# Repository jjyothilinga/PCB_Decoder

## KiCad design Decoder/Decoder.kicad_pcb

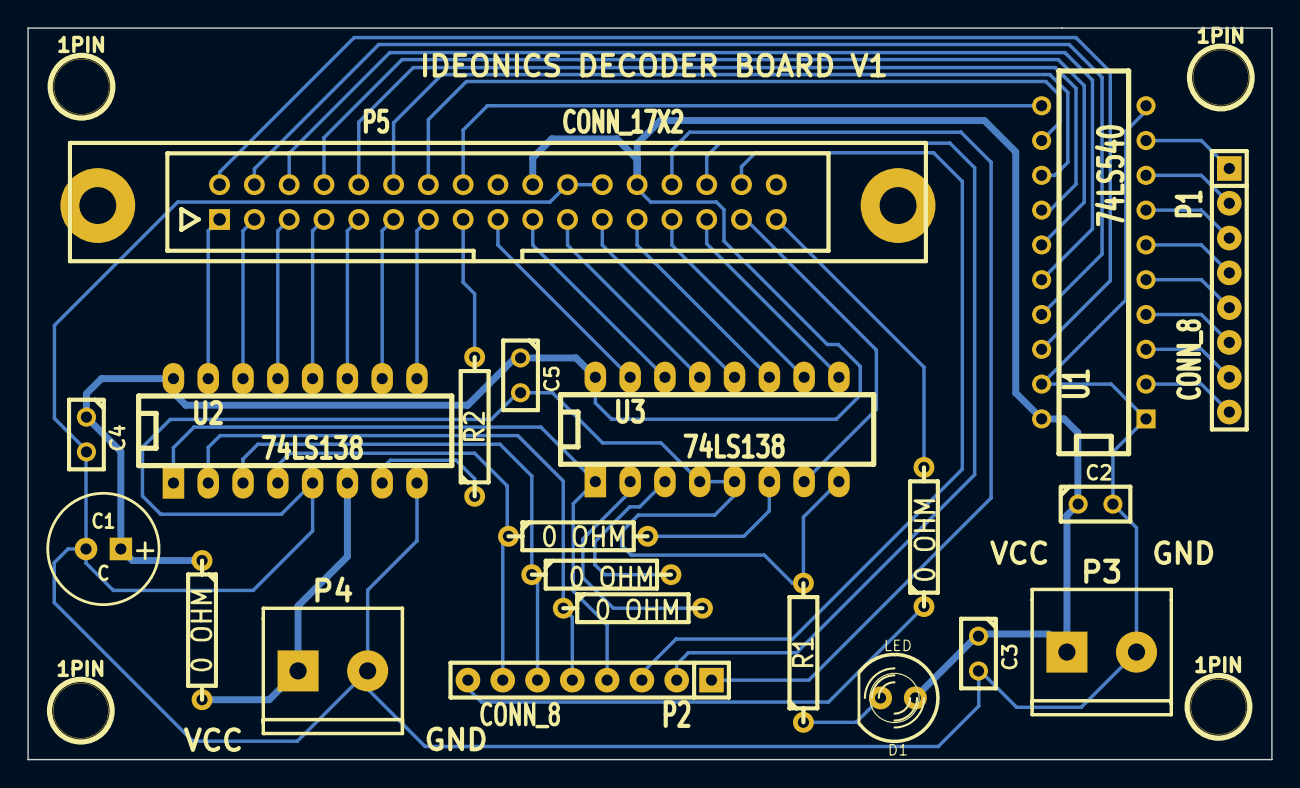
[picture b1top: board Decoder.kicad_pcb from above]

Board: 2 copper layers, 90.8 x 53.4 mm, 25 parts (0 on the bottom side), 49 nets.

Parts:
1PIN, 1PIN#2, 1PIN#3, 1PIN#4: P***; 1pin
C1: C; C1V8
C2, C3, C4, C5: C; C1
D1: LED; LED-5MM
P1, P2: CONN_8; SIL-8
P3, P4: CONN_2; mors_2p
P5: CONN_17X2; HE10_34D
R1: R; R4
R2, R3, R4, R5, R6, R7: 0 OHM; R4
U1: 74LS540; DIP-20__300
U2, U3: 74LS138; DIP-16__300_ELL

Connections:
+5V: C1.1, C2.1, C3.1, C4.1, C5.1, D1.1, P3.1, P5.20, P5.26, R7.1, U1.20, U2.6, U2.16, U3.16
/1A: P5.1, U2.15
/1B: P5.17, U3.15
/2A: P5.3, U2.14
/2B: P5.19, U3.14
/3A: P5.5, U2.13
/3B: P5.21, U3.13
/4A: P5.7, U2.12
/4B: P5.23, U3.12
/5A: P5.9, U2.11
/5B: P5.25, U3.11
/6A: P5.11, U2.10
/6B: P5.27, U3.10
/7A: P5.13, U2.9
/7B: P5.29, U3.9
/8A: R2.1, U2.7
/8B: P5.31, U3.7
/20: P2.1, P5.28
/21: P2.2, P5.30
/22: P2.3, P5.32
/30: P2.4, U2.1, U3.1
/31: P2.5, R4.1, U2.2
/32: P2.6, R5.1, U2.3
/33: P2.7, R6.1, U2.4
/34: P5.33, R3.2
/A: P5.2, U1.18
/B: P5.4, U1.17
/C: P5.6, U1.16
/D: P5.8, U1.15
/E: P5.10, U1.14
/F: P5.12, U1.13
/G: P5.14, U1.12
/H: P5.16, U1.11
GND: C1.2, C2.2, C3.2, C4.2, C5.2, P3.2, P4.2, P5.22, P5.24, R1.2, U1.1, U1.10, U1.19, U2.5, U2.8, U3.4, U3.5, U3.8
unnamed: P4.1, R7.2
unnamed: P2.8, R3.1
unnamed: P1.7, U1.3
unnamed: P1.1, U1.9
unnamed: P1.2, U1.8
unnamed: P1.3, U1.7
unnamed: P1.4, U1.6
unnamed: P1.5, U1.5
unnamed: P1.6, U1.4
unnamed: P1.8, U1.2
unnamed: R6.2, U3.6
unnamed: R5.2, U3.3
unnamed: R4.2, U3.2
unnamed: P5.15, R2.2
unnamed: D1.2, R1.1

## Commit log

2015-01-20 :confetti_ball: Added .gitattributes & .gitignore files
2015-01-20 Completed
